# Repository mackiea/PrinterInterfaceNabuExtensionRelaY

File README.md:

# PrinterInterfaceNabuExtensionRelaY (PINERY)
PINERY - A hardware interface device between the NABU PC (http://www.nabu.ca) and a Centronics/PC-compatible printer.

The NABU's parallel port is a DB-15-pin connector. Although it obviously does not match the DB-25 connector of the IBM PC/Centronics connector, most pins match, and interfacing them is a matter of mapping pins.

See https://en.wikipedia.org/wiki/Parallel_port for the Centronics parallel port protocol, and https://cloud.nabu.ca/docs/Nabu_PC_Technical_Specifications.pdf "Printer Interface" (p.7) for the NABU parallel port protocol.

## Pinouts
| Signal | NABU | DB-25 |
| ------ |-----:| -----:|
| STROBE |    1 |     1 |
| Data 0 |    2 |     2 |
| Data 1 |    3 |     3 |
| Data 2 |    4 |     4 |
| Data 3 |    5 |     5 |
| Data 4 |    6 |     6 |
| Data 5 |    7 |     7 |
| Data 6 |    8 |     8 |
| Data 7 |    9 |     9 |
| Busy   |   11 |    11 |
| Ground |   15 | 18-25 |

## Unused PC/Centronics Pins
These are optional 2.54mm connectors to allow for expanded use with fancy printers, and can be controlled via a NABU Option Card or other control.
They are  **Ack**, **Paper-Out**, **Select**, **Linefeed**, **Error**, **Reset** and **Select-Printer**.

## Unused NABU Pins
These are optional 2.54mm connectors to expose the unused NABU pins. There is no documented connection. In case they are in fact usable, or can be made usable, they can be mapped to the unused Centronics pins, or wired for some other nefarious purpose. They are pins 10 and 12-14.

## Containment Unit
This has been sized to fit the [Hammond 1551mini box](https://www.digikey.ca/en/products/detail/hammond-manufacturing/1551FBK/1090719?utm_adgroup=General&utm_source=google&utm_medium=cpc&utm_campaign=PMax%20Shopping_Product_Zombie%20SKUs&utm_term=&productid=1090719&gclid=CjwKCAjwzuqgBhAcEiwAdj5dRs3rq5Sxppuy35osANsapgPSYujJgOChvvt58ERvUnlV1GkpL7u4-hoCjrUQAvD_BwE). Doing so, with the connector tabs external to the box, should bolster the PINERY against the forces of plugging and unplugging. The box will need to be trimmed to allow the connectors to fit.

## ENID Compatibility
Although [ENID] ((https://github.com/mackiea/ExternalNabuInterfaceDevice) also uses a DB-25 interface, it is *not* compatible and is not related to this project.

## So have we tested the dang thing?
Not yet! But the pin mapping is proven to work for an [Apple Dot-Matrix (C Itoh) Printer](https://en.wikipedia.org/wiki/Apple_Dot_Matrix_Printer).

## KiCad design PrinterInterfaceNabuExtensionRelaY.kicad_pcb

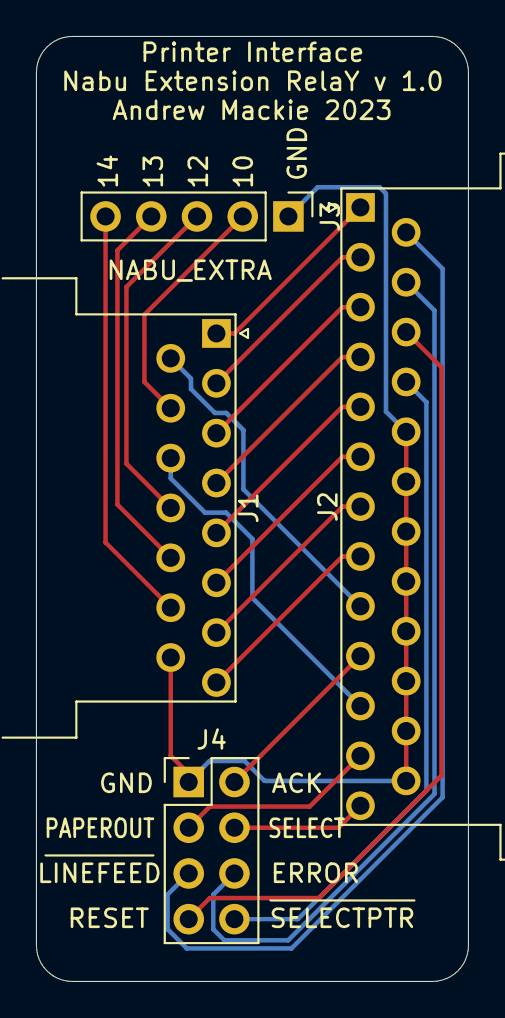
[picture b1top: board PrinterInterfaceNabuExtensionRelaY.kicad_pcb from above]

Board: 2 copper layers, 24.0 x 52.5 mm, 4 parts (0 on the bottom side), 22 nets.

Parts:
J1: DB15_POINT_TOWARDS_NABU; DSUB-15_Male_Horizontal_P2.77x2.54mm_EdgePinOffset9.40mm
J2: DB25_POINT_TOWARDS_PRINTER; DSUB-25_Female_Horizontal_P2.77x2.54mm_EdgePinOffset9.40mm
J3: NABU_EXTRA; PinHeader_1x05_P2.54mm_Vertical
J4: PRINTER_EXTRA; PinHeader_2x04_P2.54mm_Vertical

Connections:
ACK: J2.10, J4.2
BUSY: J1.11, J2.11
DATA0: J1.2, J2.2
DATA1: J1.3, J2.3
DATA2: J1.4, J2.4
DATA3: J1.5, J2.5
DATA4: J1.6, J2.6
DATA5: J1.7, J2.7
DATA6: J1.8, J2.8
DATA7: J1.9, J2.9
ERROR: J2.15, J4.6
GND: J1.15, J2.18, J2.19, J2.20, J2.21, J2.22, J2.23, J2.24, J2.25, J3.1, J4.1
LINEFEED: J2.14, J4.5
NABU10: J1.10, J3.2
NABU12: J1.12, J3.3
NABU13: J1.13, J3.4
NABU14: J1.14, J3.5
PAPEROUT: J2.12, J4.3
RESET: J2.16, J4.7
SELECT: J2.13, J4.4
SELECTPRINTER: J2.17, J4.8
STROBE: J1.1, J2.1

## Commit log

2023-03-15 Added KiCAD files.
2023-03-15 Added pretty pictures
